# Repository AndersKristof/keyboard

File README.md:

Prosjekt: Tastatur styrt med AVR mikrokontrollere

Student: Anders Kristoffersen

Veileder: Terje Mathiesen

Kontaktperson hos problemeier: Atle Dyrnes

# Innhold

1. [Problemstilling](#1-problemstilling)
    - 1.1 [Overordnet problemstilling](#11-overordnet-problemstilling)
    - 1.2 [Endelig spesifikasjon](#12-endelig-spesifikasjon)
2. [Løsning](#2-løsning)
    - 1.3 [Konsept](#13-konsept)
    - 1.4 [Maskinvare](#14-maskinvare)
        - 1.4.1 [Design](#141-design)
        - 1.4.2 [Implementasjon](#142-implementasjon)
    - 1.5 [Fastvare](#15-fastvare)
        - 1.5.1 [Design](#151-design)
        - 1.5.2 [Implementasjon](#152-implementasjon)
3. [Verifikasjon og testing](#3-verifikasjon-og-testing)
   - 1.6 [Kretstesting](#16-kretstesting)
   - 1.7 [Fastvaretesting](#17-fastvaretesting)
4. [Konklusjon](#4-konklusjon)
-  [Referanser](#referanser)
- [Vedlegg A](#vedlegg-a)
   - GitHub-depot
- [Vedlegg B](#vedlegg-b)
   - Tegninger av kretsdiagram
- [Vedlegg C](#vedlegg-c)
   - Tegninger av kretskort
- [Vedlegg D](#vedlegg-d)
   - Bilder av ferdig loddet tastatur

# 1 Problemstilling

## 1.1 Overordnet problemstilling

Å bygge et tastatur med egenutviklet fastvare og utforming spesifisert helt til ens egne
ønsker.

## 1.2 Endelig spesifikasjon

Tastaturet skal fungere i stor grad som et normalt tastatur med tall-, bokstav og vanlige
spesialtaster men med mulighet for å programmere fastvaren til det en selv ønsker.
Utformingen på tastaturet skal gi gode forhold for komfort og helse for en som bruker
tastatur i lange perioder om gangen. Tastaturet skal være styrt av en eller flere AVR
mikrokontrollere og kommunikasjon til PC skal skje over USB.

# 2 Løsning

## 1.3 Konsept

Første steg i prosjektet ble å utforske ulike løsninger som er blitt gjort tidligere. Det
vanligste valget når en skal designe sitt eget tastatur var å bruke et relativt ferdig
System On Chip (SOC) som f.eks. Pro Micro og benytte seg av ferdigutviklet fastvare som
QMK. Men her ønsket jeg heller å utvikle min egen fastvare og starte designet mitt med
utgangspunkt i en enkeltstående AVR mikrokontroller.

Den største fordelen med å utvikle egen fastvare er tilpasningsmulighetene det gir.
Derfor ønsket jeg også å inkludere noen tilkoblingsmuligheter til tastaturet som gir
muligheten til å utvikle svært frie utvidelser til tastaturet i fremtiden.

I tillegg måtte utformingen på tastaturet bestemmes og da fant jeg ut at et todelt
tastatur der tastene har parallelle kolonner passet meg best. Et todelt tastatur vil gi
større frihet i håndplassering, mens parallelle kolonner fremfor parallelle rader gir en
mer naturlig bevegelsesmønster for fingrene når tastaturet er i bruk.

For å realisere konseptet mitt trenger jeg nå å utvikle både maskinvare og fastvare.

## 1.4 Maskinvare

### 1.4.1 Design

Jeg gikk gjennom litt forskjellige design før jeg landet på et todelt tastatur med fem
rader og syv kolonner på hver. Den mengden taster har jeg sett vil gi meg alle knappene
jeg ønsker meg i tillegg til at det lar meg ha alle radene og alle kolonnene på hver sin
port perifer på mikrokontrollerene. AVR DU og DA er begge 8-bit mikrokontrollere noe
som betyr at de har 8-bits minneaddresser, og har derfor 8 pinner tilgjengelig for hver
GPIO port modul.

AVR64DU32 og AVR64DA32 ble valget av mikrokontrollere fordi jeg skulle ta i bruk
produkt utviklet av Microchip og den nye AVR DU mikrokontrolleren kommer med en
USB-modul som passer veldig bra ettersom kommunikasjon over USB med en PC er et
av kravene jeg må oppfylle. For høyresiden av tastaturet trengs ikke USBkommunikasjonsmuligheter og jeg har derfor benyttet meg av den litt eldre AVR DA
mikrokontrolleren som i de store trekkene er svært lik en AVR DU, men uten USBmodulen blir flere pinner frigjort til fremtidige utviklingsmuligheter.

USB-kommunikasjonen trenger nødvendigvis å skje gjennom en USB-kabel og for det
trenger jeg en USB-kontakt. Her valgte jeg å bruke den nyeste tilkoblingen, altså USB-C.
Etter opplesning på USB-standarden fant jeg de nødvendige koblingene for USBkontakten for at den skulle gi tastaturet det det trenger. For å få USB-kontakten til å
levere en stabil spenning på 5V til VBUS utgangen som er det vi ønsker oss, trenger en å
koble CC1 og CC2 pinnene til jord gjennom 5.1kOhm motstander.

For kommunikasjon mellom de to delene har jeg valgt å bruke I2C-protokollen. Dette er
en mye brukt standard i industrien og AVR mikrokontrollere har gode moduler som
gjør utviklingen med denne lettere. I tillegg støtter I2C opptil 1MHz
kommunikasjonshastighet som er mye raskere enn det som trengs her. Det viktigste
kriteriet til responstiden for tastaturet er at den ikke bør bemerkes av mennesket som
bruker det, og det er 1MHz mye mer enn godt nok for.

I2C-standarden er en kommunikasjonsprotokoll som benytter seg av to ledninger; med
en klokkelinje (SCL) og en datalinje (SDA). I tillegg trenger høyre del av tastaturet også
kraftforsyning, og det er naturlig å koble sammen samme sted som kommunikasjonen.
Derfor valgte jeg å bruke en fire-pols-aux-kabel for å koble de to delene sammen, med
VDD, jord, SCL og SDA på de fire ledningene.

For å realisere knappene er konseptet veldig enkelt. En bryter er koblet i serie med en
diode mellom hver kombinasjon av rad og kolonne. Hvordan dette vil la meg oppfatte
når alle de ulike knappene blir trykket kommer jeg tilbake til i større detalj i delen om
fastvare.

Jeg tok i bruk programmet KiCAD for å utvikle kretsdiagram. KiCAD kommer også med
store bibliotek av ferdiglagde symbol for ulike komponenter som gjør steget over til
implementasjon veldig smidig. Resultatet av tegningene av kretsdiagram kan sees i
Vedlegg B.

### 1.4.2 Implementasjon

For å implementere maskinvaren fortsatte jeg altså å benytte meg av KiCAD. KiCAD lar
en koble sammen symbolene man har brukt i kretsdiagramutviklingen til fotavtrykk av
faktiske komponenter og deretter plassere dem sammen og koble dem opp på et
kretskort, så mye var allerede gjort i designfasen. De største utfordringene i denne fasen
ble å finne fotavtrykk for komponenter som jeg hadde mulighet til å få tak i, samt å ta
gode valg av taster og dioder.

Når det kommer til tastevalg, er det to klare familier av taster med to ulike fotavtrykk
for kretskortet. Cherry MX taster har høyere profil og større bredde i trykkfølelse mens
Kailh taster har lavere profil. Jeg valgte å gå for Cherry MX Brown taster som er en taktil
tast, men som lager mindre lyd enn andre taktile taster, noe jeg hadde ønsket meg.

For diodene til hver tast valgte jeg å gå for 1N4148 dioder som er svært mye brukt
silikondiode som er svært lett tilgjengelig, billig og møter alle kravene vi måtte trenge.

For oppkobling av de to mikrokontrollene har jeg koblet USB-, I2C-konnektor til de
nødvendige pinnene og beholdt en port ledig på hver av dem til henholdsvis rader og
kolonner. Det er flere VDD og jord tilkoblinger på mikrokontrollorene og som anbefalt i
databladene deres er hvert VDD- og jordpar koblet sammen med en 100nF
kondensator. Utenom VUSB og jord på AVR DU, disse trenger en 470nF kondensator for
at den interne spenningsregulatoren skal kunne omgjøre 5V inngangsspenningen om til
3.3V spenningen USB-standarden bruker.

For at det skal være mulig å programmere mikrokontrollerene også etter de er loddet
fast i kretskortet har jeg dratt ut pinner for VDD, jord, UPDI og reset som er pinnene de
fleste Microchip debuggere trenger tilgang til for å kunne programmere en chip. I tillegg
har jeg valgt å inkludere en reset-krets for hver av mikrokontrollerene som er koblet
opp akkurat som anbefalt i databladene til chippene med en bryter i serie med en
resistor som begge er parallelkoblet til en kondensator. En reset-krets er en enkel måte
å få mikrokontrolleren ut av en eventuell frysning e.l. skulle det oppstå noen uventede
feil.

På det venstre kretskortet valgte jeg å legge til et potensiometer koblet til VDD og jord
med en inngang til en av mikrokontrollerens ADC innganger. I denne omgang har jeg
ikke tenkt å ta den i bruk, men i fremtiden ser jeg for meg å inkludere en del i fastvaren
som kan benytte seg av dette til å sende volumkontrollsignaler til PC.

Mens på høyre kretskort har jeg dratt ut de ubrukte pinnene til tilkoblingspinner så
disse er tilgjengelig for å slippe kreativiteten løs i fremtiden. Jeg ser for meg å f.eks.
bruke UART kommunikasjon til å kommunisere med en enkel LCD skjerm.

Tegninger av kretskortene jeg designet finner man under Vedlegg C, mens bilder av
ferdig loddet kretskort med alle delene på er under Vedlegg D.

## 1.5 Fastvare

### 1.5.1 Design

Til å begynne med tenkte jeg på hvordan jeg skulle implementere fastvarens viktigste
oppgave, nemlig å detektere ulike tastetrykk. Løsningen starter med å ha kolonnepinnene satt opp som input-pinner, mens rad-pinnene er satt opp som output-pinner.

Utfordringen kommer av at det ikke er nok pinner på mikrokontrolleren til å koble
sammen hvert par av kolonne og rad på ulike pinner, i stedet må man ha alle radene
koblet til en kolonne på samme pinne. Da oppstår problemet med at om en trykker ned
en tast vil kolonne-pinnen tasten er koblet til få beskjed om at den har gått f.eks. lav
men uten å kunne vite hvilken rad som trakk den lav.

Implementasjonen jeg har gått for fungerer slik: input-pinnene har en intern pull-up
motstand aktivert som forsikrer seg om at disse er på et høyt nivå når ingen rader er
koblet til dem. Til å starte med er også alle output-pinnene satt til å gi ut et høyt nivå, så
ingen tastetrykk vil kunne detekteres. Deretter starter PIT (Period Interrupt Timer)
modulen å gå dra én og én rad lav og om en oppdager at en kolonne blir dratt lav
sjekker man hvilken rad som på det tidspunktet er konfigurert lav og på den måten vet
man hvilket par og dermed hvilken knapp som er aktivert. Denne løsningen er basert på
Egil Rotevatn sin løsning for sitt egenutviklede tastatur «Splitbird».

I tillegg skal fastvaren håndtere kommunikasjon, både over USB til PC og over I2C
mellom de to delene. For dette tar jeg i bruk TWI (Two-Wire Interface) modulen som
finnes på både AVR DU og DA som er I2C kompatibel, og for USB-kommunikasjonen tar
jeg i bruk USB-modulen på AVR DU. For å lese hvordan disse fungerer i større detalj kan
en sjekke AVR DU og DA databladene og lese USB 2.0 spesifikasjonen, og I2C-bussspesifikasjonen som alle ligger i referanselisten.

### 1.5.2 Implementasjon

For løsningen av implementasjon av fastvaren tenkte jeg i utgangspunktet å bruke Egil
Rotevatn sin kildekode som et startpunkt ettersom det var hans løsning jeg baserte meg
på for detektering av tastetrykk, men jeg endte opp med å bruke svært lite kode derfra
og valgte heller å skrive det litt mer fra bunnen av, både for å få bedre forståelse av
koden jeg bruker og fordi mye av Egils inkluderer elementer jeg ikke bruker.

Jeg har benyttet meg av Microchip Studio for å skrive koden. Dette er et integrert
utviklingsmiljø spesielt laget for utvikling av fastvare for AVR mikrokontrollere.
For å se implementasjonsløsningen min i større detalj kan en sjekke ut GitHub depotet
under Vedlegg A, der ligger fastvarekoden under /firmware. Koden under
/firmware/usb er kode utgitt av Microchip bruk med USB-modulen.

Her holder jeg fortsatt på å utvikle mer av funksjonaliteten jeg ønsker, så GitHub
depotet vil nok utvikle seg videre, også i dagene etter denne rapporten er levert. Mens
jeg skriver dette er ikke TWI-modulen altså I2C-kommunikasjonen oppe og kjøre.

# 3 Verifikasjon og testing

## 1.6 Kretstesting

For testing av kretskort og lodding har jeg utført litt standard in-circuit testing. Har
sjekket for kortslutninger. Sjekket at spenningsnivået på VDD er tilnærmet 5V når USBkonnektoren er tilkoblet. Testet for defekte pinner på kontrolleren. Sjekket at
kapasitans- og motstandsverdiene stemmer. Her ser alt ut til å stemme.

## 1.7 Fastvaretesting

For fastvaretesting har jeg benyttet meg av testing underveis som jeg har utviklet nye
deler av fastvaren. Ved å teste at et og et nytt tillegg til koden fungerer som det skal blir
det mye lettere å oppdage hvor feilene ligger.

Jeg har god kjennskap til USART modulen på AVR kontrollere fra før så her har jeg
benyttet meg av denne for å gi meg rask tilbakemelding på om koden jeg skriver
fungerer som den skal. USART lar meg sende beskjeder fra mikrokontrolleren til en PC
og lese dem ut med verktøy som PuTTY. I tillegg kommer de fleste modulene på
mikrokontrollerene med tonnevis av statusbits jeg kan lese ut for å få et innblikk i hvor
feil ligger.

I tillegg kommer Microchip studio med veldig praktiske feilsøkingsverktøy til å lese ut
registerverdier og se løpet til koden et steg av gangen som lar meg teste koden der jeg
ønsker og se at alt skjer som forventet.
Her har jeg ikke kommet helt i mål enda og holder fortsatt på å utvikle noe av
funksjonaliteten.

# 4 Konklusjon

For å konkludere har jeg skapt et egenutviklet tastatur der maskinvare og fastvare er
designet av meg etter mine egne ønsker. Tastaturet har utforming og funksjonalitet for
å sikre god komfort og fornøyelse når jeg bruker det. Det tar i bruk to stykk AVR
mikrokontrollere og kommuniserer med PC ved bruk av USB-standarden. Alt etter
spesifikasjonen.

Fortsatt gjenstår å knytte de to delene sammen ved bruk av I2C så tastaturet kan forenes
i ett enkelt fungerende tastatur. Og i tillegg er det lagt opp til muligheten for fremtidige
utvidelsesprosjekter til tastaturet. Jeg har også en plan om å 3D-modellere en case til
tastaturet.

# Referanser
 - Microchip Technology Inc. (2020, March). AVR128DA28/32/48/64 Preliminary Data
Sheet. Retrieved from Microchip:
https://ww1.microchip.com/downloads/en/DeviceDoc/40002183A.pdf
- Microchip Technology Inc. (2024). AVR64DU28/32 Preliminary Data Sheet. Retrieved
from Microchip:
https://ww1.microchip.com/downloads/aemDocuments/documents/MCU08/P
roductDocuments/DataSheets/AVR64DU-28-32-Prelim-DataSheetDS40002548.pdf
- NXP Semiconductors. (2021, October 1). I2C-bus specification and user manual.
Retrieved from NXP: https://www.nxp.com/docs/en/user-guide/UM10204.pdf
- Rotevatn, E. (2023, April 21). SplitBird Keyboard. Retrieved from GitLab:
https://gitlab.com/printedcircuitbirds/splitbird
- USB Implementers Forum. (2024, September 27). USB 2.0 Specification. Retrieved from
USB: https://www.usb.org/document-library/usb-20-specification
- USB Implementers Forum. (2024, October 28). USB Type-C® Cable and Connector
Specification Release 2.4. Retrieved from USB: https://www.usb.org/documentlibrary/usb-type-cr-cable-and-connector-specification-release-24

# Vedlegg A

## GitHub-depot

Fastvarekoden, KiCAD-prosjekter (kretsdiagram- og kretskortfiler) og mulighet til å
følge med på og delta i videre utvikling kan finnes på
https://github.com/AndersKristof/keyboard. Dette er det ideelle startpunktet om en
ønsker å bygge eller videreutvikle tastaturet selv.

# Vedlegg B

## Tegninger av kretsdiagram

# Vedlegg C

## Tegninger av kretskort

# Vedlegg D

## Bilder av ferdig loddet tastatur

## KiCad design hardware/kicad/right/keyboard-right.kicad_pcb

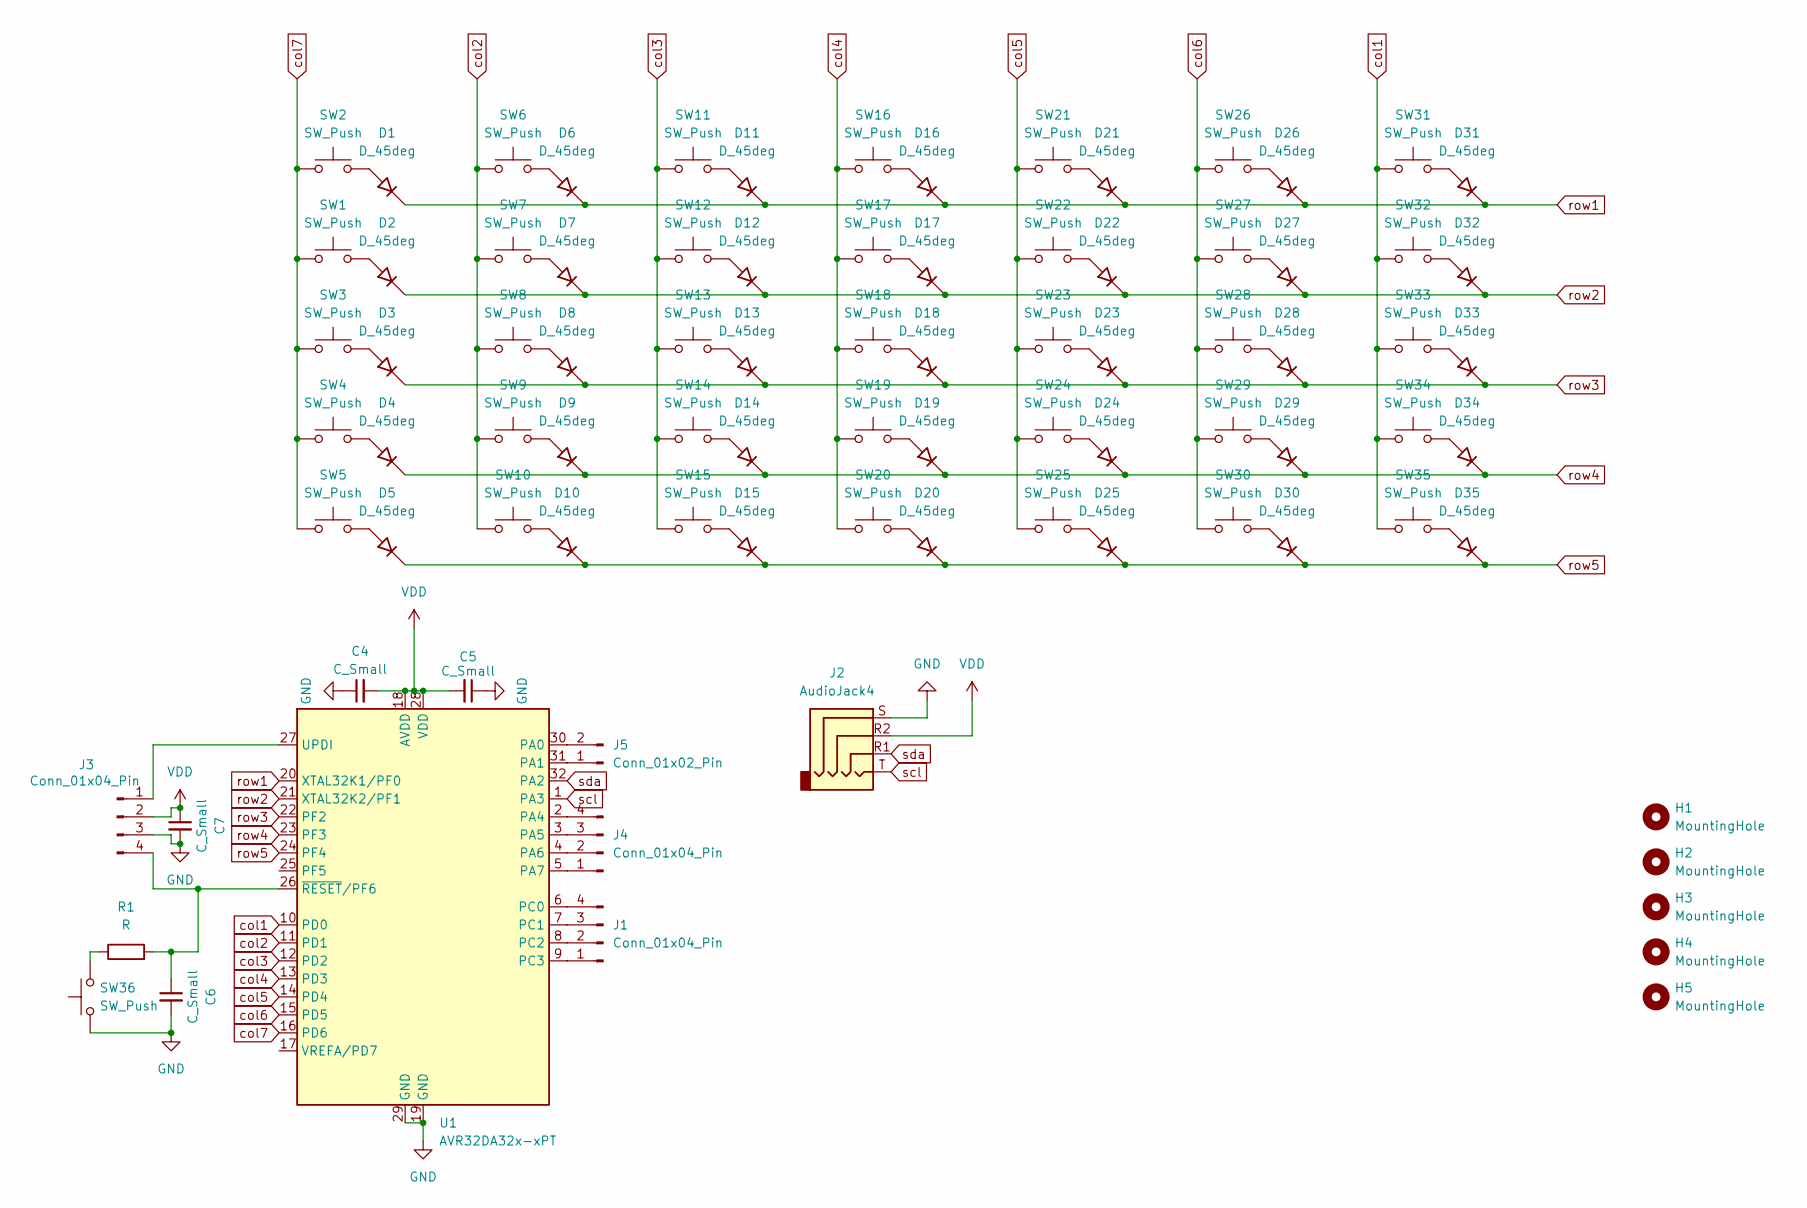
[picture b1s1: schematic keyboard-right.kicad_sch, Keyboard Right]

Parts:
C4, C5, C6, C7: C_Small; C_0603_1608Metric
D1, D2, D3, D4, D5, D6, D7, D8, D9, D10, D11, D12, D13, D14, D15, D16, D17, D18, D19, D20, D21, D22, D23, D24, D25, D26, D27, D28, D29, D30, D31, D32, D33, D34, D35: D_45deg; D_DO-35_SOD27_P3.81mm_Vertical_AnodeUp
H1, H2, H3, H4, H5: MountingHole; MountingHole_2.1mm
J1, J3, J4: Conn_01x04_Pin; FanPinHeader_1x04_P2.54mm_Vertical
J2: AudioJack4; Jack_3.5mm_CUI_SJ-3524-SMT_Horizontal
J5: Conn_01x02_Pin; PinHeader_1x02_P2.54mm_Vertical
R1: R; R_Axial_DIN0204_L3.6mm_D1.6mm_P5.08mm_Horizontal
SW1, SW2, SW3, SW4, SW5, SW34: SW_Push; SW_Cherry_MX_1.50u_PCB
SW6, SW7, SW8, SW9, SW10, SW11, SW12, SW13, SW14, SW15, SW16, SW17, SW18, SW19, SW20, SW21, SW22, SW23, SW24, SW25, SW26, SW27, SW28, SW29, SW30, SW31, SW32: SW_Push; SW_Cherry_MX_1.00u_PCB
SW33: SW_Push; SW_Cherry_MX_1.25u_PCB
SW35: SW_Push; SW_Cherry_MX_1.75u_PCB
SW36: SW_Push; SW_Tactile_SPST_NO_Straight_CK_PTS636Sx25SMTRLFS
U1: AVR32DA32x-xPT; TQFP-32_7x7mm_P0.8mm

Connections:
GND: C4.1, C5.1, C6.2, C7.2, J2.S, J3.3, SW36.1, U1.19 (GND), U1.29 (GND)
unnamed: D1.2 (A), SW2.2
unnamed: D2.2 (A), SW1.2
unnamed: D3.2 (A), SW3.2
unnamed: D4.2 (A), SW4.2
unnamed: D5.2 (A), SW5.2
unnamed: D6.2 (A), SW6.2
unnamed: D7.2 (A), SW7.2
unnamed: D8.2 (A), SW8.2
unnamed: D9.2 (A), SW9.2
unnamed: D10.2 (A), SW10.2
unnamed: D11.2 (A), SW11.2
unnamed: D12.2 (A), SW12.2
unnamed: D13.2 (A), SW13.2
unnamed: D14.2 (A), SW14.2
unnamed: D15.2 (A), SW15.2
unnamed: D16.2 (A), SW16.2
unnamed: D17.2 (A), SW17.2
unnamed: D18.2 (A), SW18.2
unnamed: D19.2 (A), SW19.2
unnamed: D20.2 (A), SW20.2
unnamed: D21.2 (A), SW21.2
unnamed: D22.2 (A), SW22.2
unnamed: D23.2 (A), SW23.2
unnamed: D24.2 (A), SW24.2
unnamed: D25.2 (A), SW25.2
unnamed: D26.2 (A), SW26.2
unnamed: D27.2 (A), SW27.2
unnamed: D28.2 (A), SW28.2
unnamed: D29.2 (A), SW29.2
unnamed: D30.2 (A), SW30.2
unnamed: D31.2 (A), SW31.2
unnamed: D32.2 (A), SW32.2
unnamed: D33.2 (A), SW33.2
unnamed: D34.2 (A), SW34.2
unnamed: D35.2 (A), SW35.2
unnamed: J1.1, U1.9 (PC3)
unnamed: J1.2, U1.8 (PC2)
unnamed: J1.3, U1.7 (PC1)
unnamed: J1.4, U1.6 (PC0)
unnamed: J3.1, U1.27 (UPDI)
unnamed: C6.1, J3.4, R1.2, U1.26 (~RESET/PF6)
unnamed: J4.1, U1.5 (PA7)
unnamed: J4.2, U1.4 (PA6)
unnamed: J4.3, U1.3 (PA5)
unnamed: J4.4, U1.2 (PA4)
unnamed: J5.1, U1.31 (PA1)
unnamed: J5.2, U1.30 (PA0)
unnamed: R1.1, SW36.2
VDD: C4.2, C5.2, C7.1, J2.R2, J3.2, U1.18 (AVDD), U1.28 (VDD)
col1: SW31.1, SW32.1, SW33.1, SW34.1, SW35.1, U1.10 (PD0)
col2: SW6.1, SW7.1, SW8.1, SW9.1, SW10.1, U1.11 (PD1)
col3: SW11.1, SW12.1, SW13.1, SW14.1, SW15.1, U1.12 (PD2)
col4: SW16.1, SW17.1, SW18.1, SW19.1, SW20.1, U1.13 (PD3)
col5: SW21.1, SW22.1, SW23.1, SW24.1, SW25.1, U1.14 (PD4)
col6: SW26.1, SW27.1, SW28.1, SW29.1, SW30.1, U1.15 (PD5)
col7: SW1.1, SW2.1, SW3.1, SW4.1, SW5.1, U1.16 (PD6)
row1: D1.1 (K), D6.1 (K), D11.1 (K), D16.1 (K), D21.1 (K), D26.1 (K), D31.1 (K), U1.20 (XTAL32K1/PF0)
row2: D2.1 (K), D7.1 (K), D12.1 (K), D17.1 (K), D22.1 (K), D27.1 (K), D32.1 (K), U1.21 (XTAL32K2/PF1)
row3: D3.1 (K), D8.1 (K), D13.1 (K), D18.1 (K), D23.1 (K), D28.1 (K), D33.1 (K), U1.22 (PF2)
row4: D4.1 (K), D9.1 (K), D14.1 (K), D19.1 (K), D24.1 (K), D29.1 (K), D34.1 (K), U1.23 (PF3)
row5: D5.1 (K), D10.1 (K), D15.1 (K), D20.1 (K), D25.1 (K), D30.1 (K), D35.1 (K), U1.24 (PF4)
scl: J2.T, U1.1 (PA3)
sda: J2.R1, U1.32 (PA2)

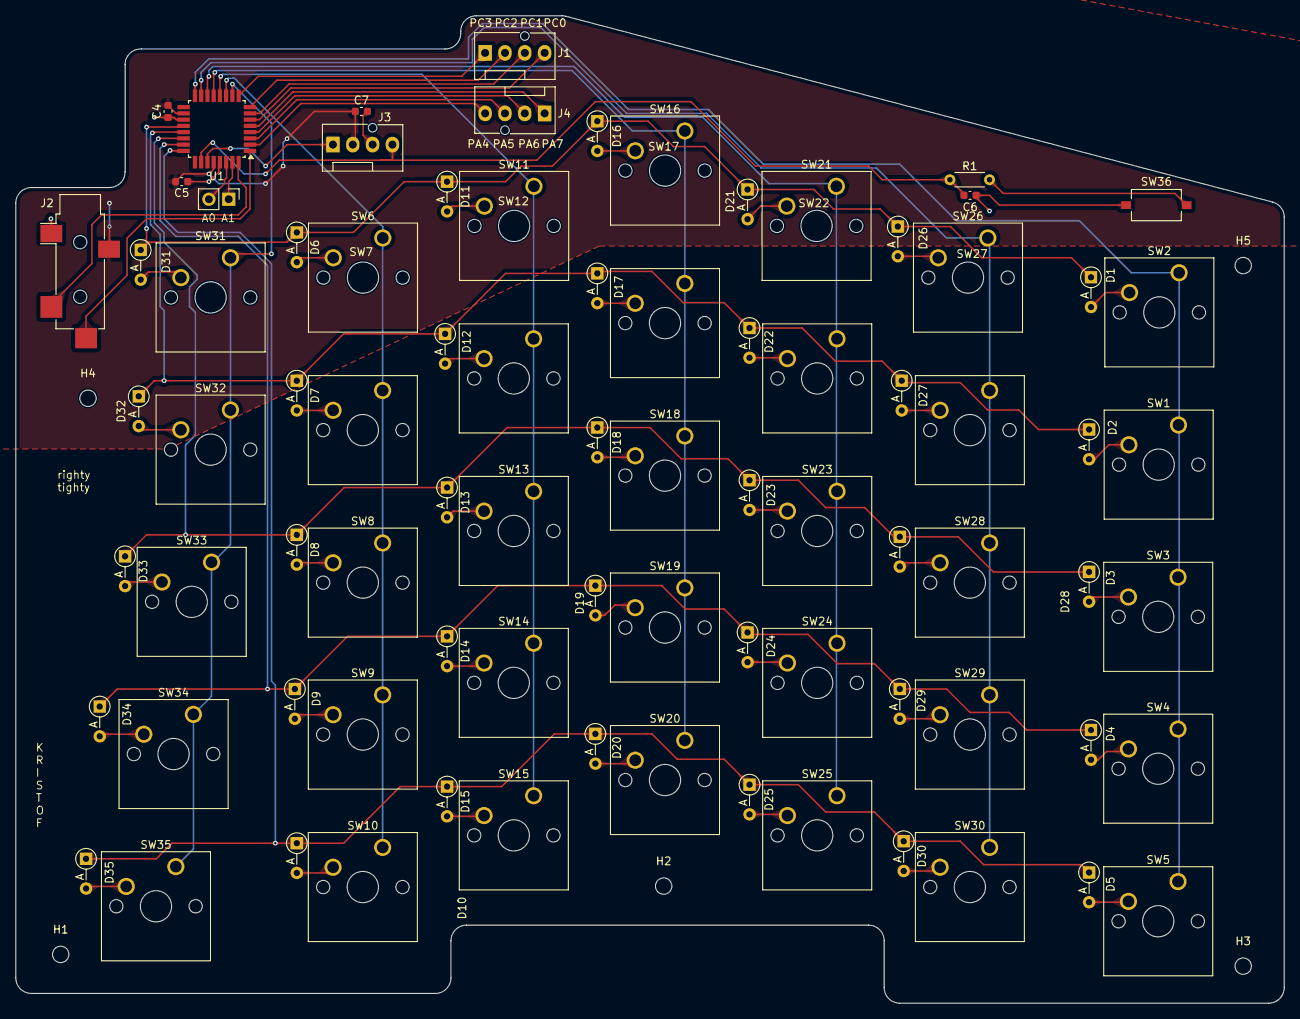
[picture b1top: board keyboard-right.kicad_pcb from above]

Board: 2 copper layers, 162.5 x 126.5 mm, 87 parts (0 on the bottom side), 64 nets.

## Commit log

2024-10-30 chore: initial commit
2024-10-30 started working on kicad schematic
2024-10-31 added AVR32DU32 datasheet and continued work on schematic and started work on pcb
2024-10-31 deleted files that were not meant to be here
2024-10-31 replaced project name from kicad to keyboard and finished (I think) the pcb
2024-10-31 saved changes to schematic
2024-10-31 finished up left-side pcb, not sure if right should go in the same project or to make a new one, plotted gerber files
2024-11-01 changed usb receptacle footprint
2024-11-03 moved kicad files to kicad/left and renamed to keyboard-left, and added kicad/right and began work on right part of keyboard there
2024-11-12 finished up right side pcb
2024-12-04 Rename AVR32DU32 Datasheet.pdf to AVR64DU32 Datasheet.pdf
2024-12-04 deleted datasheet
2024-12-04 firmware structure implemented, most taken from splitbird
2024-12-05 divided project into hardware and firmware, added word document for final report, changed mostly away from splitbird firmware and wrote my own so I have more understanding of the inner workings
2024-12-06 added da project and continued work on firmware
2024-12-06 removed word document for final report as that is delivered
2024-12-06 added readme and images, just a copy of final report for now, will transform to a more fitting readme in the future
2024-12-06 fixed formatting in readme
